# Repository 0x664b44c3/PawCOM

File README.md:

# PawCOM - a Partyline Analog (Wired) intercom system

## Scope of this project
This projects implements a partyline analog intercom system as used in the tv and event industry for interconnecting small teams of technical staff.

The system consists of any number from 2 up of so-called beltpacks, portable intercom stations plus a central power supply.
The portable parts are interconnected by generic microphone cabling (industry standard) and is electrically compatible to ClearCom, RTS and others.
Analog circuitry was inspired by the classic ClearCom MR102 and others but has been re-engineered from the ground up to use modern components and
add a few extra features.

## PAWCOM features

- analog signal processing with digital control
  - latency free
  - compressor/limiter on mic channel
  - limiter in Rx audio path (your ears will love you)
  - digitally adjustable sidetone level
  - adjustable MIC gain
  - low background noise
- Digital volume control
- digital PTT control with both latching and push to talk mode
- switchable mic power for electred mic headsets
- stereo headphone amp
- optional line in for program audio or personal music player

- click/pop free Call function
  - automatic audible call function if call is held for a certain time

## Circuit description

The beltpack consists of six main components:

- Line receiver 
- Audio mixer and headphone Amp
- Mic preamp and Line driver
- Sidetone Adjust
- Call circuitry
- System control MCU

### Line receiver
The line receiver is based around a quad opamp TL074. One gate implements the line receiver, one gate buffers the sidetone signal, the third gate generates VCC/2 (AGND) which is used througout the line interface. The last gate is unused (connected as a voltage follower with AGND on its input).

### Sidetone circuitry
Sidetone processing is located between the mic preamp (see below) and the line driver.
The sidetone signal is taken from the output of the mic preamp after the tx switch. 
It is then routed through a digital potentiometer MAX5395 and routed through the third opamp of the TL074 were its common mode voltage is translated to AGND (V+/2),
 routed through a passive filter that tries to mimic a typical line impedance, and is then applied to the inverted input of the line receiver OPAMP.

### Mic preamp and Tx switch

The mic preamp is based around an NJM2783 integrated mic preamp that includes
both preamp, switchable gain, a compressor and a buffer amplifier. The mic preamp is powered by a +9V rail generated by a LMR64010 boost converter from the +5V bus (optional, should lower the noise figure of the NJM2783 plus provide a bit more pre-compressor headroom).
The signal is then routed through a TS5A9411 analog switch (capacitive coupling is used here to bring the common mode voltage down to 2.5V) to provide a switchable  additional -10dB pad and then goes into gate 1 of an LMV358 driving 
into the MAX5359 sidetone-digipot.

The Tx signal then goes through a NE5534 driving the signal line. A last bit of filtering is applied here to provide a roll of towards higher frequencies and then driven onto the line through coupling capacitor and a 1.5kΩ resistor.

### Audio mixer

The actual audio mixer section consists of two LMV324 quad-opamps, a DS1881 digital volume control and a NJM2762 compressor/limiter IC.

The signal from the line receiver is goes through the NJM2762 compressor/limiter
and into a TS5A9411 analog switch (line mute).
The signal is then routed through a first buffer stage (gain = 6dB)
and then mixed with the beep signal from the MCU.
This stage drives onto two passive mixers/adders formed by resistor networks
that also provide a place to insert a stereo "program audio" signal into the headphones. This sum-signal is then buffered by two more LMV324 gates and drives the two halves of the DS1881 digital volume control IC.
The output signal of this digipot is buffered once more by two further opamps connected as voltage followers and then finally goes into the headphone amplifier.

### Headphone amplifier

The headphone amplifier is based around a LM4880 stereo amplifier. Currently no
further gain is applied in this stage.
The output goes through two coupling capacitors (100µ electrolytic) and then out to the headset connector. The pins on the headset connector are also connected to ground by 22kΩ resistors to allow the circuitry to reach steady state without connected headphone. This helps to avoid loud clicks upon connection the headset.

### Call circuitry

The call circuitry consists of two parts: call driver and call detector.
The call driver is based around two transistors applying a slew-rate limited, current-limited drive to the signal line of the cable.
Call detection is accomplished by a schmitt trigger built around another gate of a LMV324 with a threshold of roughly 2.5V.

### System controller

An ATMega324PB handles all control tasks in the beltpack. It includes UI (rotary encoder, PTT and call button, a few LEDs), beep tone generation and so on.
Furthermore the uC has one ADC dedicated to monitoring the supply voltage of the beltpack to detect a mic mute pulse as used by some systems.

The digital pots are controlled using an I2C bus that also routes to the front panel (where a PCF8574 port expander takes car eof driving the LEDs and rading PTT and call button status).

## Further reading and other projects about Partyline

You may have a look at the fnordcom project that has compiled a number of schematics and information around
older clearcom intercom systems: https://github.com/pc-coholic/fnordcom

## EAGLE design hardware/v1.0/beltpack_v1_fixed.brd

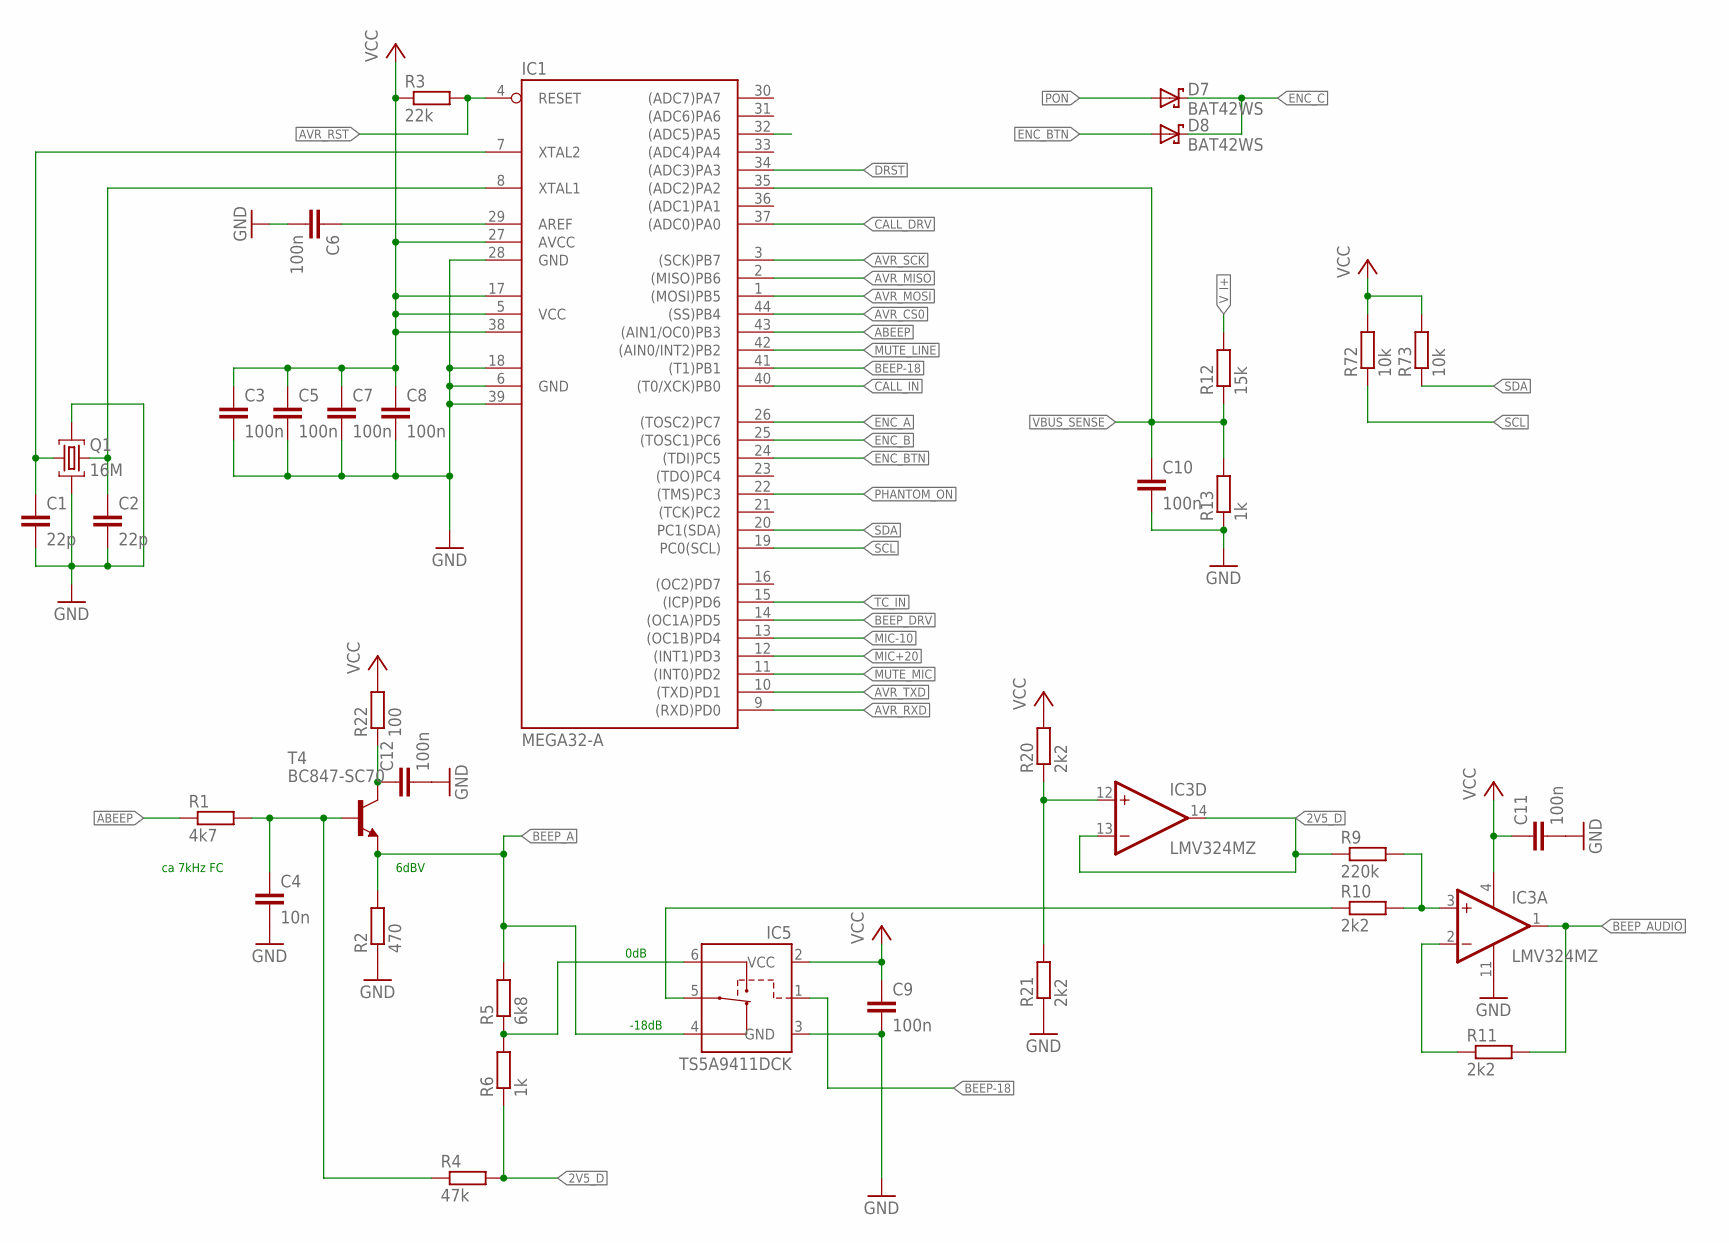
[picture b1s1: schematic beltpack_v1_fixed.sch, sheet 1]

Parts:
C1, C2: 22p; C0603
C3, C5, C6, C7, C8, C9, C10, C11, C12: 100n; C0603
C4: 10n; C0603
D7, D8: BAT42WS; SOD323R_INFINEON
IC1: MEGA32-A; TQFP44
IC3: LMV324MZ; TSSOP14
IC5: TS5A9411DCK; SC70-6L
Q1: 16M; MT
R1: 4k7; R0603
R2: 470; R0603
R3: 22k; R0603
R4: 47k; R0603
R5: 6k8; R0603
R6, R13: 1k; R0603
R9: 220k; R0603
R10, R11, R20, R21: 2k2; R0603
R12: 15k; R0603
R22: 100; R0603
R72, R73: 10k; R0603
T4: BC847-SC70; SC70

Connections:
2V5_D: IC3.13 (-IN), IC3.14 (OUT), R4.2, R6.1, R9.1
!AVR_CS0!: IC1.44 ((SS)PB4); also elsewhere on the board
!AVR_RST!: IC1.4 (RESET), R3.2; also elsewhere on the board
!CALL_IN!: IC1.40 ((T0/XCK)PB0); also elsewhere on the board
!DRST!: IC1.34 ((ADC3)PA3); also elsewhere on the board
!MUTE_LINE!: IC1.42 ((AIN0/INT2)PB2); also elsewhere on the board
!PHANTOM_ON!: IC1.22 ((TMS)PC3); also elsewhere on the board
!PON!: D7.A; also elsewhere on the board
+5VA: C12.1, R22.1, T4.3 (C)
ABEEP: IC1.43 ((AIN1/OC0)PB3), R1.1
AVR_MISO: IC1.2 ((MISO)PB6); also elsewhere on the board
AVR_MOSI: IC1.1 ((MOSI)PB5); also elsewhere on the board
AVR_RXD: IC1.9 ((RXD)PD0); also elsewhere on the board
AVR_SCK: IC1.3 ((SCK)PB7); also elsewhere on the board
AVR_TXD: IC1.10 ((TXD)PD1); also elsewhere on the board
BEEP-18: IC1.41 ((T1)PB1), IC5.1 (CTL)
BEEP_A: IC5.4 (NC), R2.2, R5.2, T4.2 (E)
BEEP_AUDIO: IC3.1 (OUT), R11.2; also elsewhere on the board
BEEP_DRV: IC1.14 ((OC1A)PD5)
CALL_DRV: IC1.37 ((ADC0)PA0); also elsewhere on the board
ENC_A: IC1.26 ((TOSC2)PC7); also elsewhere on the board
ENC_B: IC1.25 ((TOSC1)PC6); also elsewhere on the board
ENC_BTN: D8.A, IC1.24 ((TDI)PC5)
ENC_C: D7.C (K), D8.C (K); also elsewhere on the board
GND: C1.2, C2.2, C3.2, C4.2, C5.2, C6.2, C7.2, C8.2, C9.2, C10.2, C11.2, C12.2, IC1.6 (GND), IC1.18 (GND1), IC1.28 (GND), IC1.39 (GND2), IC3.11 (V-), IC5.3 (GND), Q1.2 (G1), Q1.4 (G2), R2.1, R13.1, R21.1; also elsewhere on the board
MIC+20: IC1.12 ((INT1)PD3); also elsewhere on the board
MIC-10: IC1.13 ((OC1B)PD4); also elsewhere on the board
MUTE_MIC: IC1.11 ((INT0)PD2); also elsewhere on the board
unnamed: C4.1, R1.2, R4.1, T4.1 (B)
unnamed: IC5.6 (NO), R5.1, R6.2
unnamed: IC3.12 (+IN), R20.1, R21.2
unnamed: IC3.3 (+IN), R9.2, R10.2
unnamed: IC3.2 (-IN), R11.1
unnamed: IC5.5 (COM), R10.1
unnamed: C6.1, IC1.29 (AREF)
unnamed: C1.1, IC1.7 (XTAL2), Q1.1
unnamed: C2.1, IC1.8 (XTAL1), Q1.3 (2)
SCL: IC1.19 (PC0(SCL)), R72.1; also elsewhere on the board
SDA: IC1.20 (PC1(SDA)), R73.1; also elsewhere on the board
TC_IN: IC1.15 ((ICP)PD6); also elsewhere on the board
VBUS_SENSE: C10.1, IC1.35 ((ADC2)PA2), R12.1, R13.2
VCC: C3.1, C5.1, C7.1, C8.1, C9.1, C11.1, IC1.5 (VCC), IC1.17 (VCC1), IC1.27 (AVCC), IC1.38 (VCC2), IC3.4 (V+), IC5.2 (VCC), R3.1, R20.2, R22.2, R72.2, R73.2; also elsewhere on the board
V_I+: R12.2; also elsewhere on the board

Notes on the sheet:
ca 7kHz FC
0dB
-18dB
6dBV

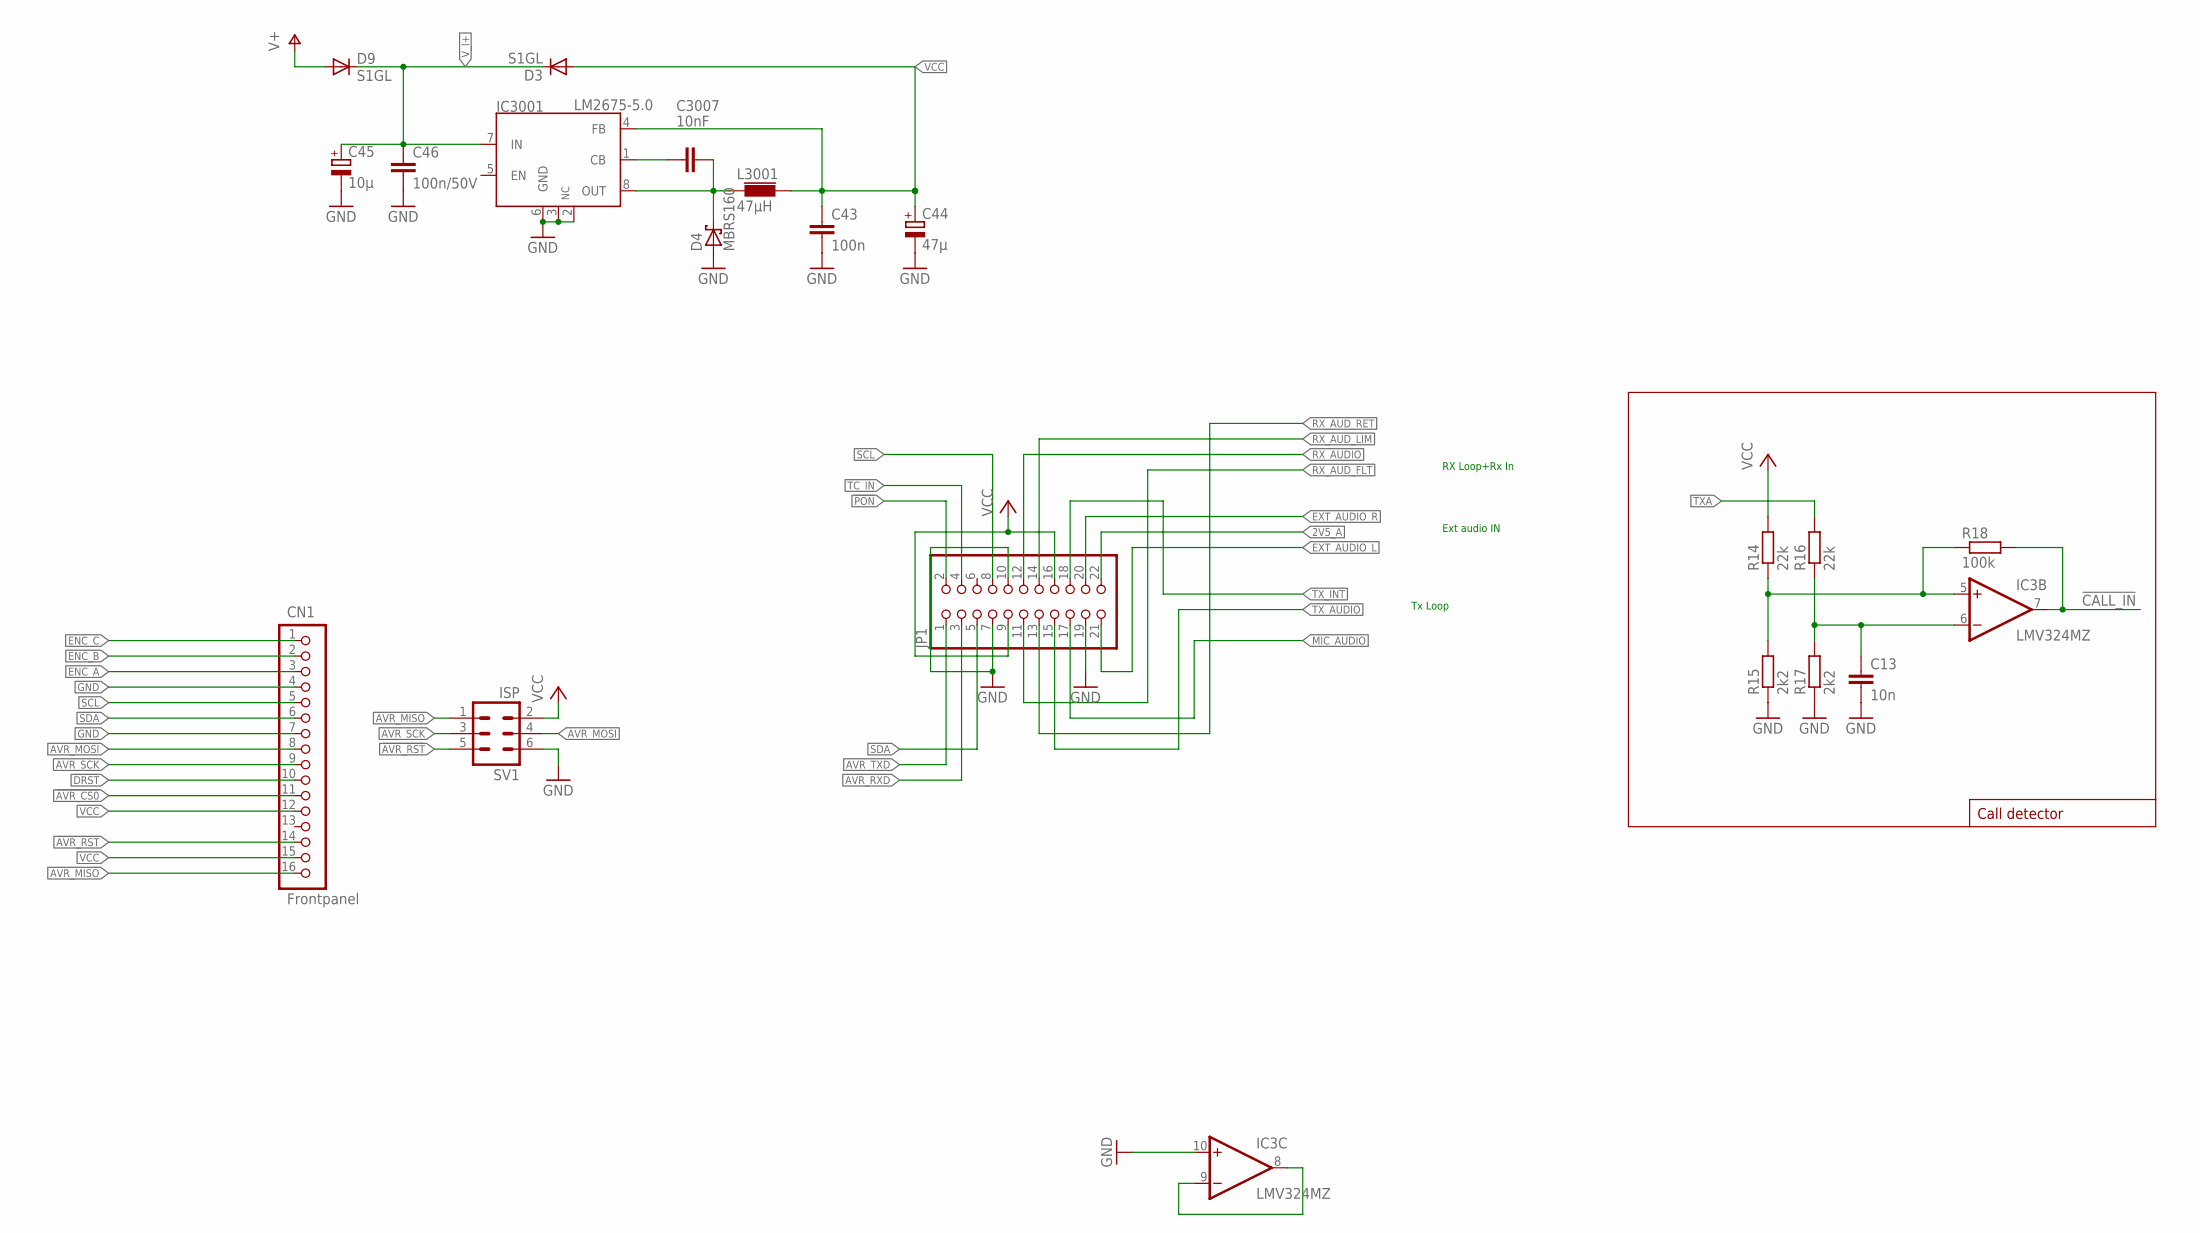
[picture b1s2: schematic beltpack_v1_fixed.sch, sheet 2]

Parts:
C13: 10n; C0603
C43: 100n; C0603
C44: 47µ; PANASONIC_B
C45: 10µ; PANASONIC_C
C46: 100n/50V; C0805
C3007: 10nF; C0805
CN1: Frontpanel; MOLEX-505278-1633
D3, D9: S1GL; DO219AB
D4: MBRS160; SMB
IC3: LMV324MZ; TSSOP14
IC3001: LM2675-5.0; SO-08
JP1: PINHD-2X11; 2X11
L3001: 47µH; PISM
R14, R16: 22k; R0603
R15, R17: 2k2; R0603
R18: 100k; R0603
SV1: ISP; ML6

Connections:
2V5_A: JP1.22; also elsewhere on the board
!AVR_CS0!: CN1.11; also elsewhere on the board
!AVR_RST!: CN1.14, SV1.5; also elsewhere on the board
!CALL_IN!: IC3.7 (OUT), R18.2; also elsewhere on the board
!DRST!: CN1.10; also elsewhere on the board
!PON!: JP1.2; also elsewhere on the board
AVR_MISO: CN1.16, SV1.1; also elsewhere on the board
AVR_MOSI: CN1.8, SV1.4; also elsewhere on the board
AVR_RXD: JP1.3; also elsewhere on the board
AVR_SCK: CN1.9, SV1.3; also elsewhere on the board
AVR_TXD: JP1.1; also elsewhere on the board
ENC_A: CN1.3; also elsewhere on the board
ENC_B: CN1.2; also elsewhere on the board
ENC_C: CN1.1; also elsewhere on the board
EXT_AUDIO_L: JP1.21; also elsewhere on the board
EXT_AUDIO_R: JP1.20; also elsewhere on the board
GND: C13.2, C43.2, C44.-, C45.-, C46.2, CN1.4, CN1.7, D4.A, IC3.10 (+IN), IC3001.2 (NC), IC3001.3 (NC), IC3001.6 (GND), JP1.7, JP1.10, JP1.19, R15.1, R17.1, SV1.6; also elsewhere on the board
MIC_AUDIO: JP1.17; also elsewhere on the board
unnamed: C3007.2, D4.C, IC3001.8 (OUT), L3001.P$1
unnamed: C3007.1, IC3001.1 (CB)
unnamed: IC3.8 (OUT), IC3.9 (-IN)
unnamed: C13.1, IC3.6 (-IN), R16.1, R17.2
unnamed: IC3.5 (+IN), R14.1, R15.2, R18.1
RX_AUDIO: JP1.12; also elsewhere on the board
RX_AUD_FLT: JP1.11; also elsewhere on the board
RX_AUD_LIM: JP1.14; also elsewhere on the board
RX_AUD_RET: JP1.13; also elsewhere on the board
SCL: CN1.5, JP1.8; also elsewhere on the board
SDA: CN1.6, JP1.5; also elsewhere on the board
TC_IN: JP1.4; also elsewhere on the board
TXA: R16.2; also elsewhere on the board
TX_AUDIO: JP1.15; also elsewhere on the board
TX_INT: JP1.18; also elsewhere on the board
V+: D9.A; also elsewhere on the board
VCC: C43.1, C44.+, CN1.12, CN1.15, D3.A, IC3001.4 (FB), JP1.9, JP1.16, L3001.P$2, R14.2, SV1.2; also elsewhere on the board
V_I+: C45.+, C46.1, D3.C, D9.C, IC3001.7 (IN); also elsewhere on the board

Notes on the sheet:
Call detector
Ext audio IN
RX Loop+Rx In
Tx Loop

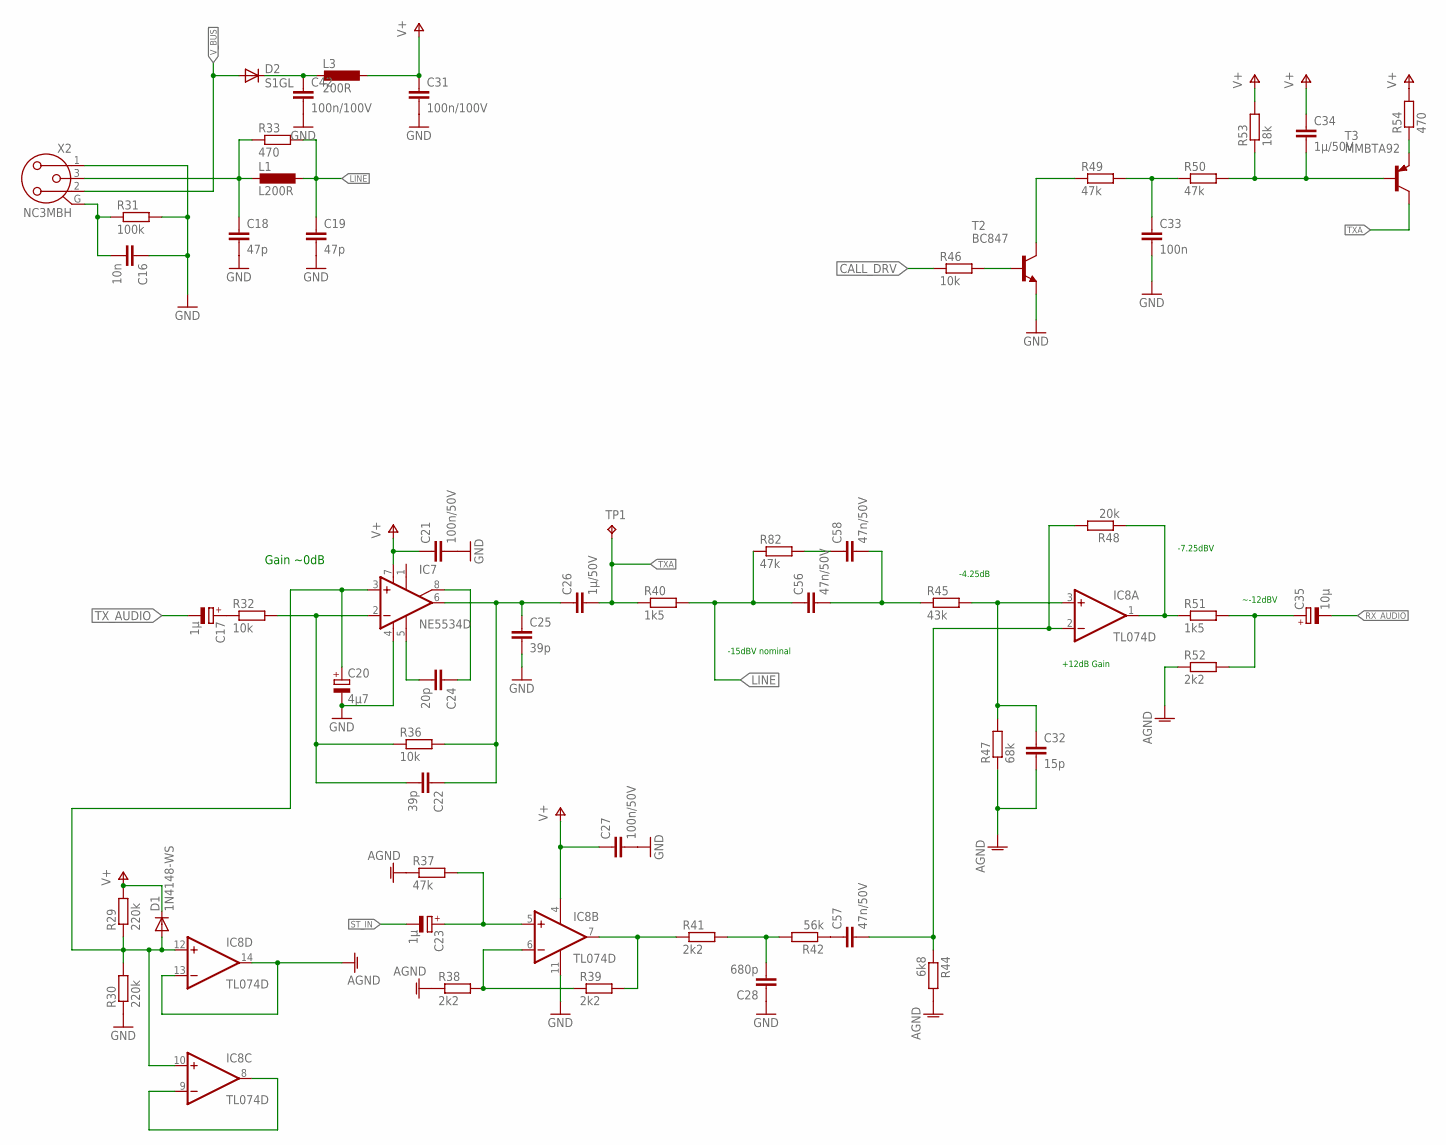
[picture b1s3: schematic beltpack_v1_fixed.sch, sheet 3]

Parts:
C16: 10n; C0805
C17, C23: 1µ; PANASONIC_B
C18, C19: 47p; C0603
C20: 4µ7; PANASONIC_B
C21, C27: 100n/50V; C0805
C22, C25: 39p; C0603
C24: 20p; C0603
C26, C34: 1µ/50V; C1206
C28: 680p; C0603
C31, C42: 100n/100V; C1206
C32: 15p; C0603
C33: 100n; C0603
C35: 10µ; PANASONIC_B
C56, C57, C58: 47n/50V; C_PAN_ECHU_E1
D1: 1N4148-WS; SOD323
D2: S1GL; DO219AB
IC7: NE5534D; SO08
IC8: TL074D; SO14
L1: L200R; R0805
L3: 200R; R0805
R29, R30: 220k; R0603
R31: 100k; R0805
R32, R36, R46: 10k; R0603
R33: 470; R0603
R37, R49, R50, R82: 47k; R0603
R38, R39, R41, R52: 2k2; R0603
R40: 1k5; R1206
R42: 56k; R0603
R44: 6k8; R0603
R45: 43k; R0603
R47: 68k; R0603
R48: 20k; R0603
R51: 1k5; R0603
R53: 18k; R0603
R54: 470; R0805
T2: BC847; SOT23
T3: MMBTA92; SOT23
TP1: XA; B1,27
X2: NC3MBH

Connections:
AGND: C32.2, IC8.13 (-IN), IC8.14 (OUT), R37.1, R38.1, R44.2, R47.1, R52.1
CALL_DRV: R46.1; also elsewhere on the board
GND: C16.1, C18.2, C19.2, C20.-, C21.2, C25.2, C27.2, C28.1, C31.2, C33.2, C42.2, IC7.4 (V-), IC8.11 (V-), R30.1, R31.2, T2.2 (E), X2.1; also elsewhere on the board
LINE: C19.1, C56.1, L1.1, R33.2, R40.2, R82.1
unnamed: C24.2, IC7.5 (CMP)
unnamed: C24.1, IC7.8 (ON/CMP)
unnamed: C22.2, IC7.2 (-IN), R32.2, R36.1
unnamed: C17.+, R32.1
unnamed: C22.1, C25.1, C26.1, IC7.6 (OUT), R36.2
unnamed: C20.+, D1.A, IC7.3 (+IN), IC8.10 (+IN), IC8.12 (+IN), R29.1, R30.2
unnamed: R46.2, T2.1 (B)
unnamed: C16.2, R31.1, X2.G
unnamed: C58.1, R82.2
unnamed: C28.2, R41.2, R42.2
unnamed: C32.1, IC8.3 (+IN), R45.2, R47.2
unnamed: C18.1, L1.2, R33.1, X2.3
unnamed: C35.+, R51.2, R52.2
unnamed: C57.2, IC8.2 (-IN), R44.1, R48.2
unnamed: C57.1, R42.1
unnamed: C42.1, D2.C, L3.2
unnamed: C56.2, C58.2, R45.1
unnamed: R54.1, T3.2 (E)
unnamed: C34.2, R50.2, R53.1, T3.1 (B)
unnamed: C33.1, R49.2, R50.1
unnamed: R49.1, T2.3 (C)
unnamed: IC8.1 (OUT), R48.1, R51.1
unnamed: IC8.7 (OUT), R39.2, R41.1
unnamed: IC8.6 (-IN), R38.2, R39.1
unnamed: C23.+, IC8.5 (+IN), R37.2
unnamed: IC8.8 (OUT), IC8.9 (-IN)
RX_AUDIO: C35.-; also elsewhere on the board
ST_IN: C23.-; also elsewhere on the board
TXA: C26.2, R40.1, T3.3 (C), TP1.TP; also elsewhere on the board
TX_AUDIO: C17.-; also elsewhere on the board
V+: C21.1, C27.1, C31.1, C34.1, D1.K (C), IC7.7 (V+), IC8.4 (V+), L3.1, R29.2, R53.2, R54.2; also elsewhere on the board
V_BUS: D2.A, X2.2

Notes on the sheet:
-15dBV nominal
+12dB Gain
-4.25dB
-7.25dBV
~-12dBV
Gain ~0dB

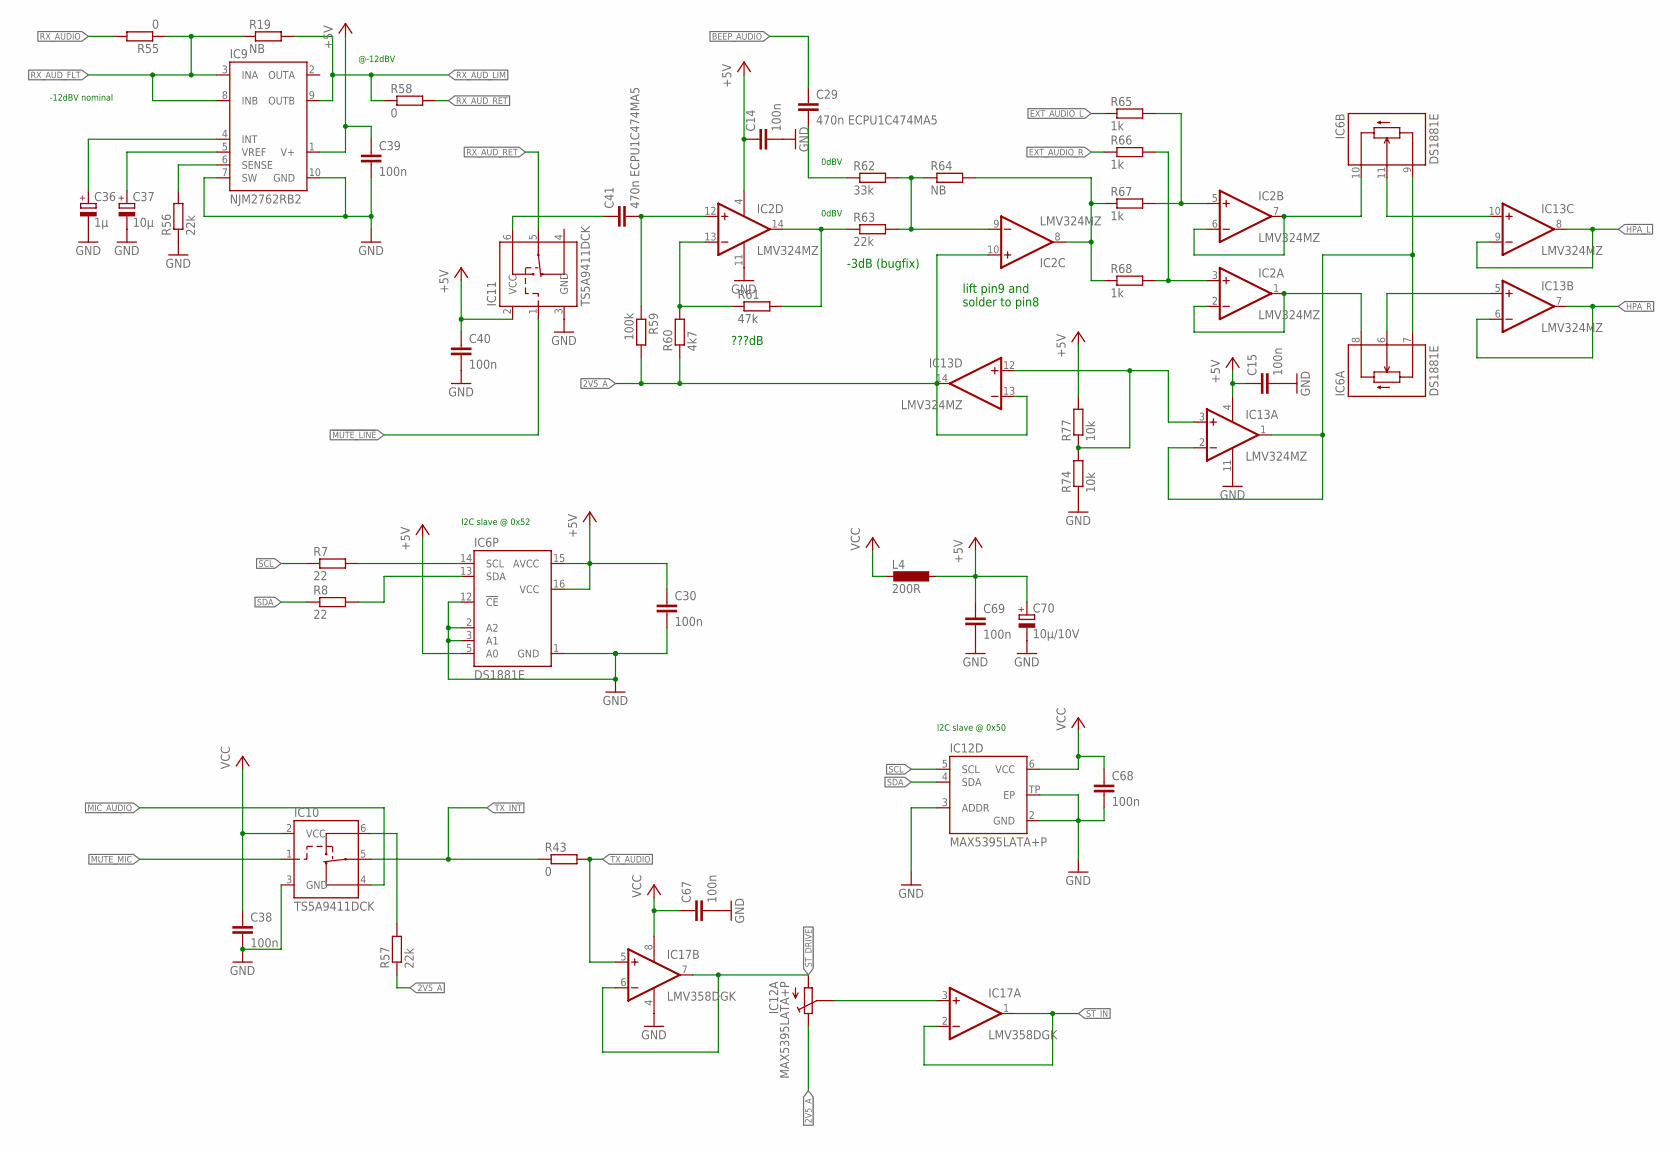
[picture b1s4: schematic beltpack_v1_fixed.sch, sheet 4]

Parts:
C14, C15, C30, C39, C40, C67, C68, C69: 100n; C0603
C29, C41: 470n ECPU1C474MA5; C_PANASONIC_H3
C36: 1µ; PANASONIC_B
C37: 10µ; PANASONIC_B
C38: 100n; C0402
C70: 10µ/10V; A/3216-18R
IC2, IC13: LMV324MZ; TSSOP14
IC6: DS1881E; TSSOP16
IC9: NJM2762RB2; MSOP10
IC10, IC11: TS5A9411DCK; SC70-6L
IC12: MAX5395LATA+P; 8TDFN-EP
IC17: LMV358DGK; VSOP8
L4: 200R; R0805
R7, R8: 22; R0402
R19, R64: NB; R0603
R43, R55, R58: 0; R0603
R56, R57, R63: 22k; R0603
R59: 100k; R0603
R60: 4k7; R0603
R61: 47k; R0603
R62: 33k; R0603
R65, R66, R67, R68: 1k; R0603
R74, R77: 10k; R0603

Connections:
2V5_A: IC2.10 (+IN), IC12.8 (E), IC13.13 (-IN), IC13.14 (OUT), R57.1, R59.2, R60.1; also elsewhere on the board
!MUTE_LINE!: IC11.1 (CTL); also elsewhere on the board
+5V: C14.1, C15.1, C30.1, C39.1, C40.1, C69.1, C70.+, IC2.4 (V+), IC6.5 (A0), IC6.15 (AVCC), IC6.16 (VCC), IC9.1 (V+), IC11.2 (VCC), IC13.4 (V+), L4.1, R77.2
BEEP_AUDIO: C29.1; also elsewhere on the board
EXT_AUDIO_L: R65.1; also elsewhere on the board
EXT_AUDIO_R: R66.1; also elsewhere on the board
GND: C14.2, C15.2, C30.2, C36.-, C37.-, C38.2, C39.2, C40.2, C67.2, C68.2, C69.2, C70.-, IC2.11 (V-), IC6.1 (GND), IC6.2 (A2), IC6.3 (A1), IC6.12 (!CE!), IC9.7 (SW), IC9.10 (GND), IC10.3 (GND), IC11.3 (GND), IC12.2 (GND), IC12.3 (ADDR), IC12.TP (EP), IC13.11 (V-), IC17.4 (V-), R56.1, R74.1; also elsewhere on the board
HPA_L: IC13.8 (OUT), IC13.9 (-IN); also elsewhere on the board
HPA_R: IC13.6 (-IN), IC13.7 (OUT); also elsewhere on the board
MIC_AUDIO: IC10.4 (NC); also elsewhere on the board
MIX_L: IC2.6 (-IN), IC2.7 (OUT), IC6.10 (H)
MIX_R: IC2.1 (OUT), IC2.2 (-IN), IC6.8 (H)
MUTE_MIC: IC10.1 (CTL); also elsewhere on the board
unnamed: IC6.11 (W), IC13.10 (+IN)
unnamed: IC6.6 (W), IC13.5 (+IN)
unnamed: IC6.14 (SCL), R7.2
unnamed: IC6.13 (SDA), R8.2
unnamed: IC6.7 (L), IC6.9 (L), IC13.1 (OUT), IC13.2 (-IN)
unnamed: IC13.3 (+IN), IC13.12 (+IN), R74.2, R77.1
unnamed: C29.2, R62.1
unnamed: C41.1, IC11.6 (NO)
unnamed: IC2.13 (-IN), R60.2, R61.1
unnamed: C36.+, IC9.4 (INT)
unnamed: C37.+, IC9.5 (VREF)
unnamed: IC2.14 (OUT), R61.2, R63.1
unnamed: IC9.6 (SENSE), R56.2
unnamed: C41.2, IC2.12 (+IN), R59.1
unnamed: IC2.9 (-IN), R62.2, R63.2, R64.1
unnamed: IC2.8 (OUT), R64.2, R67.1, R68.1
unnamed: IC2.5 (+IN), R65.2, R67.2
unnamed: IC2.3 (+IN), R66.2, R68.2
unnamed: IC10.6 (NO), R57.2
unnamed: IC12.7 (S), IC17.3 (+IN)
RX_AUDIO: R55.2; also elsewhere on the board
RX_AUD_FLT: IC9.3 (INA), IC9.8 (INB), R19.1, R55.1; also elsewhere on the board
RX_AUD_LIM: IC9.9 (OUTB), R19.2, R58.1; also elsewhere on the board
RX_AUD_RET: IC11.5 (COM), R58.2; also elsewhere on the board
SCL: IC12.5 (SCL), R7.1; also elsewhere on the board
SDA: IC12.4 (SDA), R8.1; also elsewhere on the board
ST_DRIVE: IC12.1 (A), IC17.6 (-IN), IC17.7 (OUT)
ST_IN: IC17.1 (OUT), IC17.2 (-IN); also elsewhere on the board
TX_AUDIO: IC17.5 (+IN), R43.2; also elsewhere on the board
TX_INT: IC10.5 (COM), R43.1; also elsewhere on the board
VCC: C38.1, C67.1, C68.1, IC10.2 (VCC), IC12.6 (VCC), IC17.8 (V+), L4.2; also elsewhere on the board

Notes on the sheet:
0dBV
@-12dBV
-12dBV nominal
I2C slave @ 0x50
I2C slave @ 0x52
lift pin9 and solder to pin8
???dB
-3dB (bugfix)

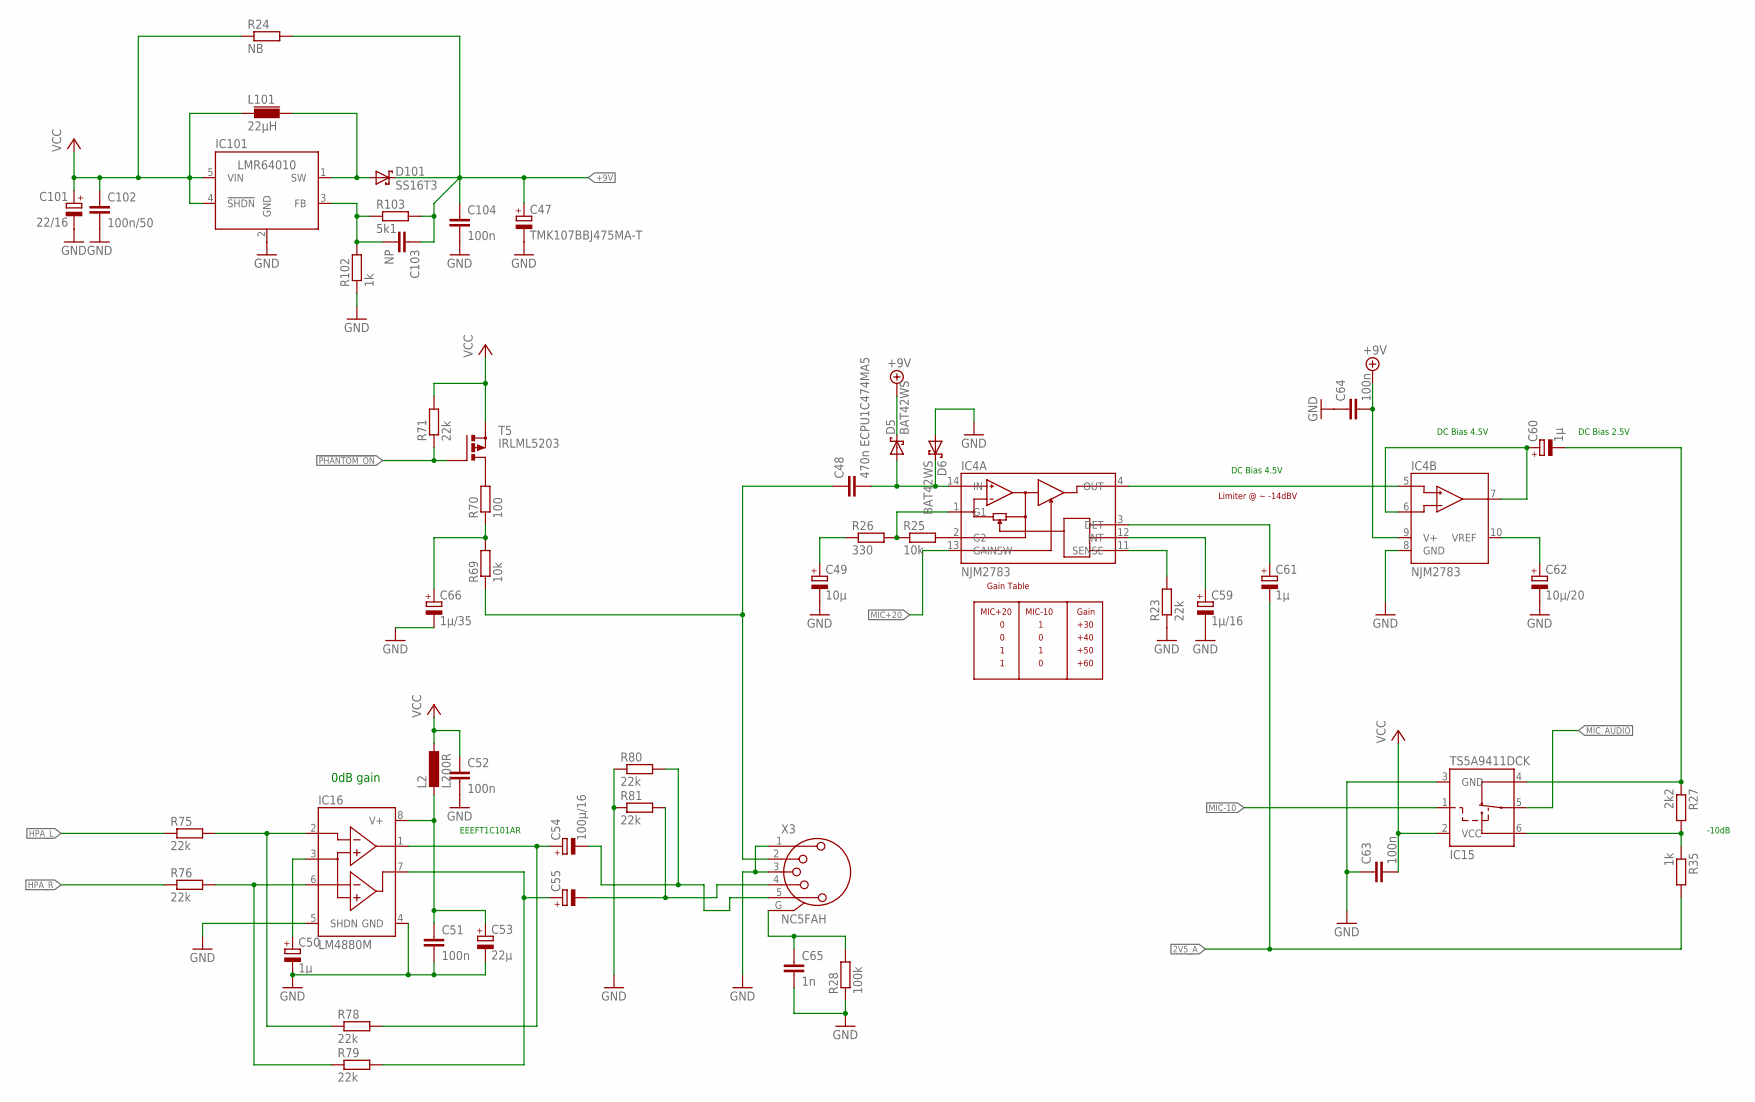
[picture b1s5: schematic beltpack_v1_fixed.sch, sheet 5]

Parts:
C47: TMK107BBJ475MA-T; PANASONIC_B
C48: 470n ECPU1C474MA5; C_PANASONIC_H3
C49: 10µ; PANASONIC_B
C50, C60, C61: 1µ; PANASONIC_B
C51, C52, C64, C104: 100n; C0603
C53: 22µ; PANASONIC_C
C54, C55: 100µ/16; PANASONIC_C
C59: 1µ/16; A/3216-18R
C62: 10µ/20; B/3528-21R
C63: 100n; C0402
C65: 1n; C0603
C66: 1µ/35; B/3528-21R
C101: 22/16; B/3528-21R
C102: 100n/50; C0805
C103: NP; C0603
D5, D6: BAT42WS; SOD323R_INFINEON
D101: SS16T3; SMA
IC4: NJM2783; TSSOP14
IC15: TS5A9411DCK; SC70-6L
IC16: LM4880M; SOIC8
IC101: LMR64010; SOT23-5
L2: L200R; R0805
L101: 22µH; PISG
R23, R71, R75, R76, R78, R79, R80, R81: 22k; R0603
R24: NB; R0603
R25, R69: 10k; R0603
R26: 330; R0603
R27: 2k2; R0603
R28: 100k; R0603
R35, R102: 1k; R0603
R70: 100; R0603
R103: 5k1; R0603
T5: IRLML5203; SOT23
X3: NC5FAH

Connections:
2V5_A: C61.-, R35.2; also elsewhere on the board
!PHANTOM_ON!: R71.1, T5.1 (G); also elsewhere on the board
+9V: C47.+, C64.2, C103.1, C104.1, D5.C (K), D101.C (K), IC4.9 (V+), R24.2, R103.2
GND: C47.-, C49.-, C50.-, C51.2, C52.2, C53.-, C59.-, C62.-, C63.1, C64.1, C65.2, C66.-, C101.-, C102.2, C104.2, D6.A, IC4.8 (GND), IC15.3 (GND), IC16.4 (GND), IC16.5 (SHDN), IC101.2 (GND), R23.1, R28.1, R80.1, R81.1, R102.1, X3.1, X3.3; also elsewhere on the board
HPA_L: R75.1; also elsewhere on the board
HPA_R: R76.1; also elsewhere on the board
MIC: C48.1, R69.1, X3.2
MIC+20: IC4.13 (GAINSW); also elsewhere on the board
MIC-10: IC15.1 (CTL); also elsewhere on the board
MIC_AUDIO: IC15.5 (COM); also elsewhere on the board
unnamed: C54.+, IC16.1 (OUTA), R78.2
unnamed: C55.+, IC16.7 (OUTB), R79.2
unnamed: C103.2, IC101.3 (FB), R102.2, R103.1
unnamed: C55.-, R81.2, X3.4
unnamed: C54.-, R80.2, X3.5
unnamed: C50.+, IC16.3 (BYPASS)
unnamed: C48.2, D5.A, D6.C (K), IC4.14 (IN)
unnamed: IC4.2 (G2), R25.2
unnamed: IC4.1 (G1), R25.1, R26.2
unnamed: C49.+, R26.1
unnamed: C59.+, IC4.12 (INT)
unnamed: C65.1, R28.2, X3.G
unnamed: C51.1, C53.+, IC16.8 (V+), L2.2
unnamed: C61.+, IC4.3 (DET)
unnamed: IC4.4 (OUT), IC4.5 (BUFIN)
unnamed: IC4.11 (SENSE), R23.2
unnamed: C60.+, IC4.6 (BUFG), IC4.7 (BUFO)
unnamed: IC15.6 (NO), R27.2, R35.1
unnamed: C66.+, R69.2, R70.1
unnamed: C60.-, IC15.4 (NC), R27.1
unnamed: C62.+, IC4.10 (VREF)
unnamed: R70.2, T5.3 (D)
unnamed: IC16.6 (INB), R76.2, R79.1
unnamed: IC16.2 (INA), R75.2, R78.1
SW_HV: D101.A, IC101.1 (SW), L101.P$2
VCC: C52.1, C63.2, C101.+, C102.1, IC15.2 (VCC), IC101.4 (!SHDN!), IC101.5 (VIN), L2.1, L101.P$1, R24.1, R71.2, T5.2 (S); also elsewhere on the board

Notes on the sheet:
EEEFT1C101AR
DC Bias 4.5V
DC Bias 2.5V
-10dB
Gain Table
MIC+20
MIC-10
Gain
+30
+40
+50
+60
Limiter @ ~ -14dBV
0dB gain

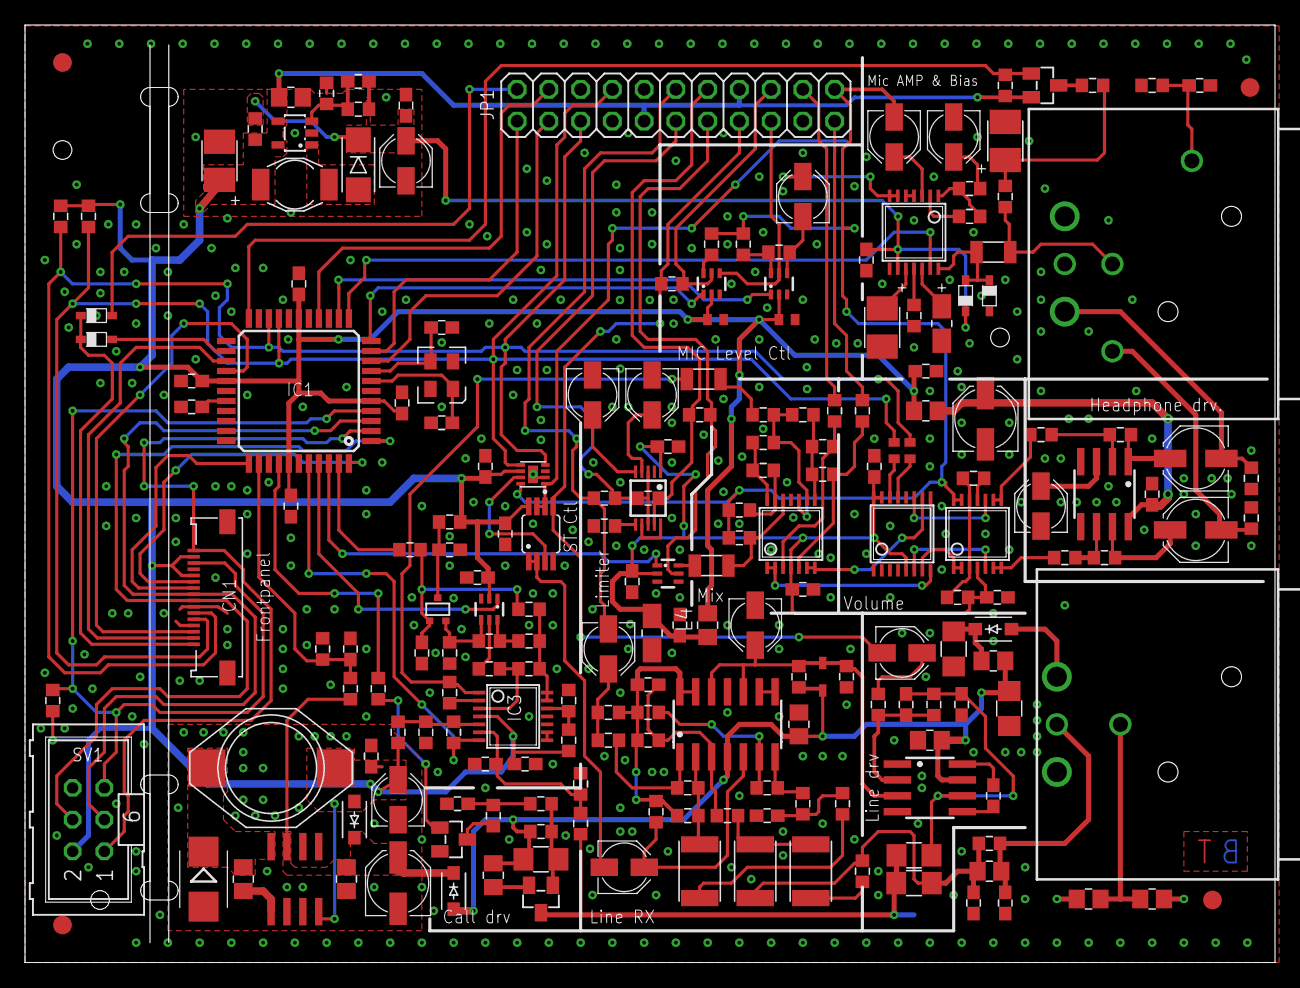
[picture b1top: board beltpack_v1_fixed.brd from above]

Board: 2 copper layers, 100.0 x 75.0 mm, 207 parts (1 on the bottom side), 142 nets.

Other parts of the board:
U$1, U$2, U$3, U$4: FIDUCIAL_G15

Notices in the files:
parts and their libraries:
dicons: Copyright (C) 2004, Bob Starr (rtzaudio@mindspring.com)
